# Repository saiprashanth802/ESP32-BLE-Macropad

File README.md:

# ESP32 BLE HID MacroPad

> An open-source, battery-powered wireless BLE HID macro pad built on ESP32 with NimBLE stack. Hand-wired with a custom FDM-printed enclosure, fully self-contained shortcut controller with an on-device UI — no companion app required.

---

## Versions

Every version lives side by side in this repo — `firmware/v4/`, `firmware/v5/`,
`cad/stl/v5/` and so on. **`main` is always the latest working state**; released
versions are marked with **git tags**, so you can grab any of them:

```bash
git clone https://github.com/saiprashanth802/ESP32-BLE-Macropad.git
git checkout v4.1     # or v5.0 — see Releases for downloadable zips
```

| Version | Tag | Status | Description |
|---------|-----|--------|-------------|
| v3 | — | ✅ Complete | 8-button, ST7735 128×160, ESP32-BLE-Keyboard — flagship build |
| v4 | `v4.1` | ✅ Stable | NimBLE stack, ghost connection fix, BUILD MODE |
| v4 + Media Remote | — | 🔬 Testing | Wireless AS5600 scroll wheel via ESP-NOW |
| v5 | `v5.0` | ✅ Built & Running | 12-key MX matrix, ST7789 240×320, multi-host BLE, robot face, Windows companion app |
| v5.1 | `v5.1` | ✅ Current | Local-LLM rewrite menu driven from the pad, wireless encoder puck complete |

---

## v3 — Flagship Build

> Primary portfolio entry. 8-button macro pad with ST7735 display, NimBLE BLE HID, and on-device preset switching with BUILD MODE.

### Build Photos

| | |
|---|---|
|  |  |
| Assembled v3 | Internal wiring |

| | |
|---|---|
|  |  |
| Enclosure CAD | Encoder knob CAD |

### Hardware
- ESP32 WROOM-32
- ST7735 128×160 TN display
- 8× tactile switches in 4×2 layout
- EC11 rotary encoder + custom skull knob
- TP4056 + 18650 2600mAh battery
- M3 corner studs with heat-set inserts
- Hand-wired, FDM printed enclosure (PLA, 0.2mm, 20% gyroid)

### Features
- 8 presets: OnShape, KiCad, Music, Gaming, LTspice, SYS, DEV, EDIT
- BUILD MODE — remap any button live (hold encoder 1.5s)
- Encoder modes: VOL / SCROLL / ZOOM / ALT-TAB
- Settings menu: brightness, sleep timeout, sensitivity, OS layout
- OS Layout: Windows / Linux — remaps shortcuts live
- RTOS light-sleep with GPIO wakeup
- Wake-key buffer + reconnect HUD
- BLE bond clear (hold encoder 3s)
- Estimated battery life: 3–4 months typical desk use

### GPIO Allocation (v3/v4)

| GPIO | Function |
|------|----------|
| 14,13,26,25,22,21,35,19 | 8× buttons |
| 2, 4 | Encoder CLK, DT |
| 15 | Encoder SW |
| 5, 17, 16, 12 | TFT CS, DC, RST, BL |
| 23, 18 | SPI MOSI, SCLK |

---

## v4 — Current Stable

> Migrated to NimBLE-Arduino to fix persistent BLE ghost-connection bug on Windows sleep/wake cycles.

### Key Changes from v3
- NimBLE-Arduino replaces ESP32-BLE-Keyboard
- GAP-layer callbacks for reliable connect/disconnect tracking
- 1N5819 Schottky diode on VIN rail isolating charger from USB supply
- `esp_sleep_disable_wakeup_source()` before re-arming GPIO wakeup each cycle
- `ledcAttach()` called on every wake to restore PWM backlight
- Firmware: `macropad_v4_nimble_espnow.ino`

### TFT_eSPI User_Setup.h

```cpp
#define ST7735_DRIVER
#define TFT_CS   5
#define TFT_DC   17
#define TFT_RST  16
#define TFT_WIDTH  128
#define TFT_HEIGHT 160
#define TFT_MOSI 23
#define TFT_SCLK 18
```

---

## Media Remote — Test Phase

> Standalone wireless scroll wheel using AS5600 magnetic encoder. Connects to v4 macropad via ESP-NOW or directly to PC via BLE HID. Designed for high-resolution smooth scrolling with velocity-based acceleration.

### Hardware
- ESP32 NodeMCU dev board
- AS5600 magnetic rotary encoder (I2C, 12-bit resolution, 4096 steps/rev)
- Custom 3D printed enclosure with bearing-mounted 50mm scroll wheel
- Diametrically magnetized cylinder magnet on axle
- 3× tactile buttons — Play/Pause, Next, Prev

### Design & Prototype

| | |
|---|---|
|  |  |
| Enclosure CAD | Scroll wheel with bearing mount CAD |

*Prototype — printed enclosure with 50mm scroll wheel, AS5600 underneath, wired to NodeMCU ESP32S*

### Features
- Velocity-accelerated volume control — slow turn = fine steps, fast spin = large jumps
- Adjustable sensitivity 1–10, saved to NVS
- Hold Btn1 + turn wheel = adjust sensitivity live
- Hold Btn1 + Btn3 for 1.5s = toggle ESP-NOW ↔ BLE mode
- Mode and sensitivity persist across power cycles
- LED blink feedback: 1 blink = ESP-NOW, 3 blinks = BLE

### Modes

| Mode | Description |
|------|-------------|
| BLE HID | Connects directly to PC as "MediaRemote" |
| ESP-NOW | Sends to v4 macropad which relays via BLE to PC |

### Wiring

| Pin | GPIO | Function |
|-----|------|----------|
| AS5600 SDA | 21 | I2C data |
| AS5600 SCL | 22 | I2C clock |
| BTN1 Play/Pause | 27 | INPUT_PULLUP → GND |
| BTN2 Next | 26 | INPUT_PULLUP → GND |
| BTN3 Prev | 25 | INPUT_PULLUP → GND |
| LED | 2 | Onboard LED |

---

## v5 — Built & Running

> Full redesign, **assembled and working**. 12-key MX mechanical switch matrix (4×3 landscape), ST7789 240×320 IPS display, **multi-host BLE with 3 device slots (Logitech Easy-Switch style)**, a state-reactive robot face with personalities, and a Windows companion app that turns the pad into a Stream Deck.

### Build Photos

| | |
|---|---|
|  |  |
| Assembled v5 — printed case, spiral-top keycaps, blue accent lighting | Top-down: 4×3 MX grid and the 2" IPS display |

*The screen shows the pad's two live features at once: the procedural robot eyes in
their default robotic blue, and the now-playing strip — track title with a progress
bar and elapsed/total time, streamed from the host by the companion app.*

**Print files:** [`cad/stl/v5/`](cad/stl/v5) — three case parts plus the switch plate.

### Multi-Host BLE — use it like a Pebble Keys
- 3 host slots, each remembers one bonded device (NVS persisted across power cycles)
- Hold **FN (K9) 1s** → tap **K1/K2/K3** to jump between paired devices
- Hold the slot key 1.5s instead to (re-)pair that slot with a new device
- **Each slot advertises its own static-random BLE address**, so every host stores an independent bond. This is what makes the slots real: with one shared identity, two OSes dual-booting the same machine present the *same* controller MAC, collapse onto one slot, and each re-pair overwrites the other's link key — the endless forget-and-re-pair loop
- Switching re-advertises **open** (no accept-list — whitelist filtering breaks reconnection from resolvable private addresses); a bonded host that belongs to a different slot is rejected in software
- Status bar shows the three slots like Easy-Switch LEDs (green = connected, amber = waiting, magenta = pairing)
- Firmware: `firmware/v5/macropad_v5.ino` (NimBLE 2.x API, single file)

### Face — state-reactive robot eyes / GIF screensaver
- Procedural eyes that react to device state: blink when idle-connected, dart when disconnected, widen in pairing mode, glance toward the slot on Easy-Switch, droop before sleep
- **Expression packs**: every eye parameter (color, geometry, blink/glance timing) is JSON in the config API — the companion app can generate personalities without reflashing
- Or upload a looping **GIF** (≤ ~700 KB) through the web UI as an ambient screensaver
- Settings → FACE (OFF/IDLE/ALWAYS) and STYLE (EYES/GIF); first press always just wakes, never types
- Custom partition table: dual 1.5 MB OTA slots + 896 KB SPIFFS for animations

### Rewrite Menu — local LLM text tools, driven from the pad
- Select text anywhere, press a key on the pad, pick a style — the pad rewrites it in place
- Styles: formalise, casualise, shorten, clarify, fix spelling/grammar, summarise, expand rough notes into an email, or treat the selection as a prompt and answer it
- Runs against a local **[Ollama](https://ollama.com)** instance, so **nothing leaves the machine** unless a style is deliberately pointed at a hosted model
- Prompts, temperature, reasoning and per-style model live in a **hot-reloaded `styles.json`** — tune them without a rebuild
- Pad shows the style picker, then ACCEPT / REGEN / CANCEL; the side-by-side preview on screen is editable before you accept
- Built entirely on the existing host-link opcodes — **no firmware changes required**
- A **fine-tuned FIX model** was trained for this and measured against the general-purpose
  one across two sizes and four epoch counts. It wins on corrections and speed and loses on
  restraint, which is the axis that decides — so it did not ship, and the lab is in the repo
  anyway: [`ml/`](ml) and [`docs/FIX_MODEL_FINETUNE.md`](docs/FIX_MODEL_FINETUNE.md)
- Full guide: [`docs/REWRITE_MENU.md`](docs/REWRITE_MENU.md) · Linux setup:
  [`docs/LINUX_REWRITE_SETUP.md`](docs/LINUX_REWRITE_SETUP.md)

### Companion App — Windows and Linux

> The pad works standalone. The companion turns it into a Stream Deck: it launches
> and focuses apps from a key press, streams now-playing to the pad's screen,
> switches presets to follow the foreground window, feeds the puck a real volume
> number, and drives the rewrite menu.

- Two front-ends over one shared **.NET 9** core — `MacroPadDeck.Core` holds the wire
  protocol, profiles and orchestration; `MacroPadDeck` is WinRT/SMTC/WPF, and
  `MacroPadDeck.Linux` is BlueZ/MPRIS/X11/GTK3
- **Install, build and run:** [`companion/README.md`](companion/README.md) — .NET 9 SDK
  per platform, the dependencies, pairing, the publish command, and what each failure
  in `deck.log` means

### Config Mode — wireless setup + OTA firmware update
- **Settings → CONFIG (WiFi/OTA)** suspends BLE and raises a WiFi hotspot (`MacroPad-Setup` / `macropad123`, `http://192.168.4.1`)
- Built-in web UI + JSON API to remap keys, edit presets, and change settings — no re-flash needed
- Every key can be a built-in action, an **arbitrary modifier+keycode chord**, a media code, a **type-a-string**, or a **multi-step macro** — the schema a companion app targets
- **OTA firmware update**: upload a new `.bin` from the browser; it flashes the inactive OTA partition and reboots (safe rollback if it fails)
- WiFi and BLE never run at once (WROOM-32 coexistence); entering/leaving Config Mode reboots cleanly
- Full contract: [`docs/CONFIG_API.md`](docs/CONFIG_API.md)

### Wireless Encoder Puck — a dial that isn't attached to anything

| | |
|---|---|
|  |  |
| The puck beside the v5 — a separate battery-powered device, no cable between them | 50 mm dial in the two-part printed housing |

- **Separate device**, talks to the pad over **ESP-NOW** — no cable, no second BLE connection to manage
- **AS5600 magnetic angle sensor** — 12-bit, contactless, nothing mechanical to wear out. The magnet is diametrically magnetised and sits in a pocket in the dial
- **The pad owns the dial mode** (VOLUME / ZOOM). The puck renders whatever it's told and never self-changes, so a pad key and the puck can't disagree
- **Volume is pushed, never estimated.** BLE HID volume is relative — the pad sends up/down and is never told the level — so the companion reading Windows Core Audio is the only way either device knows a real number
- **Deep sleep when unlinked**, waking on rotation. The AS5600 has no motion interrupt, so waking is timer-poll-and-look with a movement threshold, which stops a knock or thermal drift waking it
- **Sealed housing with no reset button** — spinning the dial a few turns while unlinked reboots it. Gated strictly on being unlinked, since spinning hard is completely ordinary during normal volume use
- Wiring: [`hardware/puck_wiring.md`](hardware/puck_wiring.md) · Protocol: [`docs/PUCK_PROTOCOL.md`](docs/PUCK_PROTOCOL.md) · Print files: [`cad/stl/puck/`](cad/stl/puck)

### Hardware Spec
- NodeMCU ESP32-S V1.1 (WROOM-32) dev board
- ST7789 240×320 IPS display, landscape mount, glass flush-mounted (30.6×40.8mm active area)
- 12× MX compatible mechanical switches, plate mount, 4×3 landscape matrix, 19.05mm pitch
- 12× 1N4148 diodes for n-key rollover (cathode → row line — see `hardware/pin_reference_v5.md`)
- Wireless encoder puck: AS5600 + 50mm bearing-mounted dial, ESP-NOW (separate device — **built and working**; see [`hardware/puck_wiring.md`](hardware/puck_wiring.md) and [`docs/PUCK_PROTOCOL.md`](docs/PUCK_PROTOCOL.md))
- CKCS charge+boost module + 18650 cell
- Custom copper-tape ridge substrate PCB

### Enclosure
- 115×95×30mm main body
- Encoder dial lobe: half-proud right edge, 50mm diameter, 25mm proud (XP-Pen style)
- Screen: 31.0×41.2mm flush glass window, 35.2×48.4mm module ledge 2.1mm deep
- Bottom cover: M3 screws into brass heat-set inserts, 4× corners

### PCB Technique — Copper Tape Ridge Substrate
3D printed plate with elevated ridges as trace isolation guides. A single copper sheet is laid over the entire surface — the ridges act as cutting guides. Scalpel-cut along ridge edges isolates traces. Looks like a real PCB, built from scratch.

### v5 GPIO Allocation

| GPIO | Board Label | Function | Notes |
|------|------------|----------|-------|
| 18 | P18 | TFT SCK | SPI clock |
| 23 | P23 | TFT MOSI | ST7789 SDA |
| 5  | P5  | TFT CS  | |
| 21 | P21 | TFT DC  | |
| 22 | P22 | TFT RST | |
| 19 | P19 | TFT BL  | PWM via LEDC |
| 25 | P25 | Matrix Row 1 | Driven LOW to scan |
| 26 | P26 | Matrix Row 2 | Driven LOW to scan |
| 27 | P27 | Matrix Row 3 | Driven LOW to scan |
| 32 | P32 | Matrix Row 4 | Driven LOW to scan |
| 33 | P33 | Matrix Col 1 | INPUT_PULLUP |
| 13 | P13 | Matrix Col 2 | INPUT_PULLUP |
| 14 | P14 | Matrix Col 3 | INPUT_PULLUP |

> Zero strapping pins used — clean boot every time, no pull resistors needed for boot. No I2C or encoder switch on the main board — the AS5600 puck is wireless. Full details + diode orientation: `hardware/pin_reference_v5.md`.

---

## Repository Structure

```
ESP32-BLE-MacroPad/
├── firmware/
│   ├── v4/macropad_v4_nimble_espnow.ino   — v4 + optional ESP-NOW
│   ├── v5/
│   │   ├── macropad_v5/                   — v5 multi-host firmware + partition table
│   │   ├── puck_encoder/                  — wireless encoder puck (ESP32)
│   │   ├── puck_encoder_8266/             — puck on ESP-12E
│   │   └── User_Setup.h                   — TFT_eSPI config for the ST7789
│   ├── media_remote/                      — BLE + ESP-NOW scroll wheel
│   └── tests/                             — per-peripheral bring-up sketches
├── companion/
│   ├── README.md                          — install / build / run — start here
│   ├── MacroPadDeck.Core/                 — protocol, profiles, controller (net9.0)
│   ├── MacroPadDeck/                      — Windows front-end (WinRT/WPF)
│   └── MacroPadDeck.Linux/                — Linux front-end (BlueZ/MPRIS/GTK3)
├── ml/                                    — the FIX fine-tune lab: data generator,
│                                            eval harness, training configs, runbook
├── cad/stl/                               — print files: v5 case, keycaps, puck
├── hardware/
│   ├── pin_reference_v5.md                — complete v5 GPIO table + diode orientation
│   ├── puck_wiring.md                     — encoder puck wiring
│   ├── kicad/                             — KiCad project + fab gerbers
│   ├── datasheets/                        — ESP-12E
│   └── ESP32_DevKitC_v4.kicad_mod         — custom KiCad footprint
├── docs/
│   ├── CONFIG_API.md                      — host-link opcodes and the JSON config API
│   ├── REWRITE_MENU.md                    — local-LLM text tools
│   ├── LINUX_REWRITE_SETUP.md             — ydotool / Wayland one-time setup
│   ├── FIX_MODEL_FINETUNE.md              — the fine-tune, measured, and why it lost
│   ├── PUCK_PROTOCOL.md                   — ESP-NOW protocol v3
│   └── ROADMAP.md · TESTING_LOG.md
├── scripts/setup-ydotool.sh
└── README.md
```

---

## Dependencies

| Library | Purpose |
|---------|---------|
| NimBLE-Arduino | BLE HID stack |
| TFT_eSPI | Display driver |
| Preferences | NVS persistent storage |
| Wire | I2C for AS5600 |
| esp_now | ESP-NOW for media remote |

Companion app (see [`companion/README.md`](companion/README.md)):

| Requirement | Purpose |
|---------|---------|
| .NET 9 SDK | Builds all three companion projects |
| BlueZ / WinRT | BLE host link to the pad |
| GTK3 + libayatana-appindicator | Linux tray and editor |
| MPRIS / SMTC | Now-playing source |
| Ollama (optional) | Local model behind the rewrite menu |

---

## Key Learnings

- **NimBLE vs ESP32-BLE-Keyboard** — NimBLE with GAP callbacks is required for reliable connect/disconnect tracking. The Arduino BLE stack returns false positives after Windows sleep/wake.
- **GPIO 12 strapping pin** — Must read LOW at boot. Avoided entirely in v5 by moving TFT backlight to GPIO 19.
- **LEDC + BLE init order** — BLE radio init resets the LEDC peripheral. Always call `ledcAttach()` after `NimBLEDevice::init()`.
- **WiFi + BLE coexistence** — ESP-NOW and NimBLE share the antenna. Made optional in v4 (toggle in settings) to avoid connection instability.
- **ST7789 RAM constraint** — Full 240×320 16-bit sprite = 153KB, too large for WROOM-32 with BLE active. Solution: direct TFT drawing with small reusable sprites.
- **Input-only GPIOs** — GPIO 34, 35, 36, 39 have no internal pullups. Always use external 10kΩ resistors.

---

## License

**CC BY-NC 4.0** — Free to use and modify for personal and non-commercial purposes only. Commercial use requires explicit written permission from the author.

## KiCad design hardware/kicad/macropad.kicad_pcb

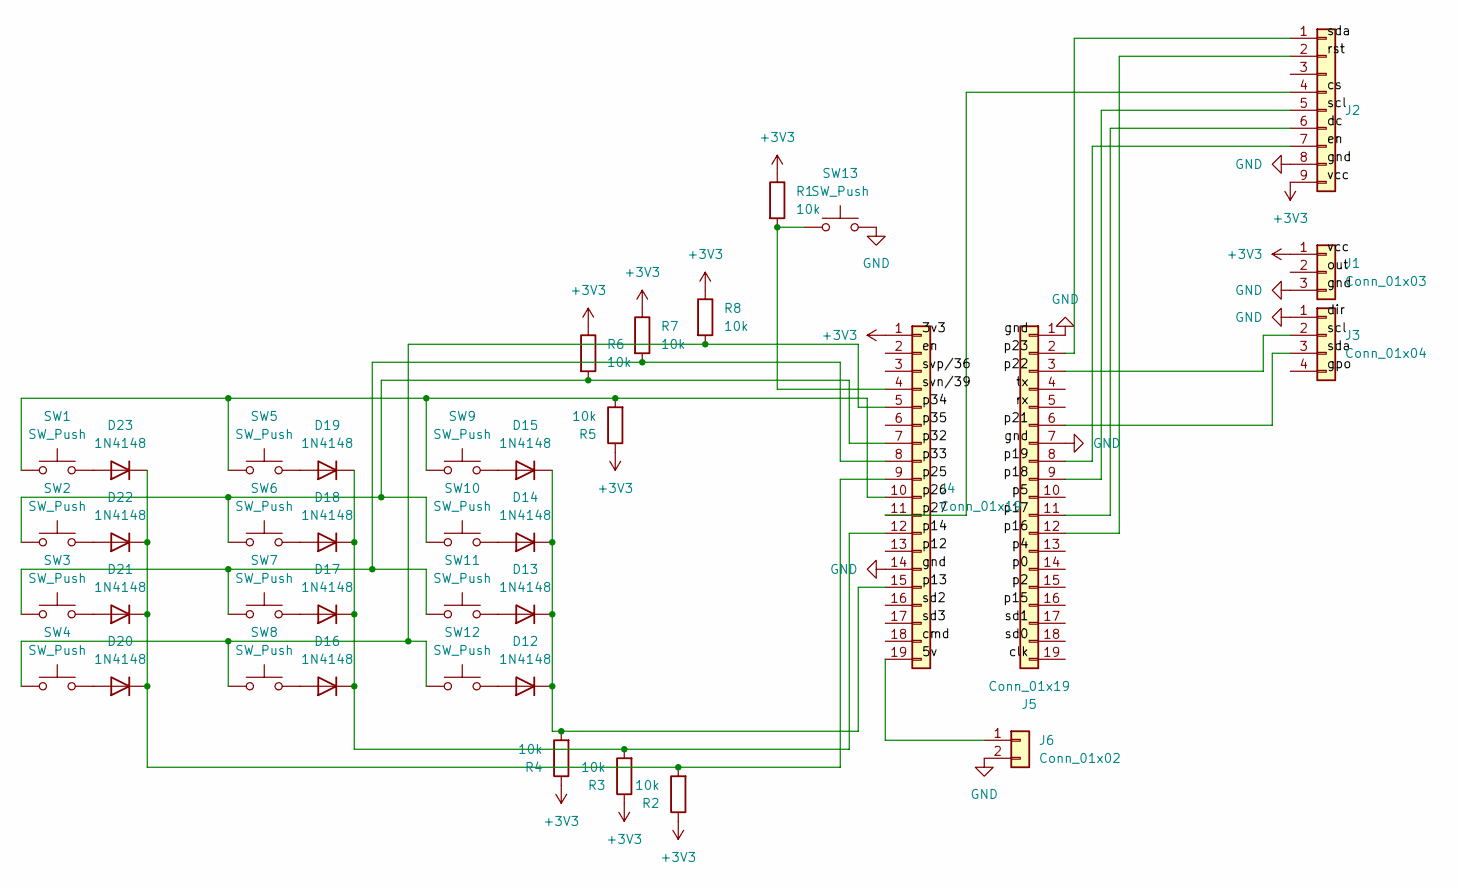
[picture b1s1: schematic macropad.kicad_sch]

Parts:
D12, D13, D14, D15, D16, D17, D18, D19, D20, D21, D22, D23: 1N4148; D_DO-35_SOD27_P7.62mm_Horizontal
J1: Conn_01x03; PinHeader_1x03_P2.54mm_Vertical
J2: Conn_01x09; PinHeader_1x09_P2.54mm_Vertical
J3: Conn_01x04; PinHeader_1x04_P2.54mm_Vertical
J4, J5: Conn_01x19; PinHeader_1x19_P2.54mm_Horizontal
J6: Conn_01x02; PinHeader_1x02_P2.54mm_Horizontal
R1, R2, R3, R4, R5, R6, R7, R8: 10k; R_Axial_DIN0207_L6.3mm_D2.5mm_P7.62mm_Horizontal
SW1, SW2, SW3, SW4, SW5, SW6, SW7, SW8, SW9, SW10, SW11, SW12: SW_Push; SW_Cherry_MX_1.00u_PCB
SW13: SW_Push; SW_PUSH_6mm_H4.3mm

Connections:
+3V3: J1.1, J2.9, J4.1, R1.1, R2.1, R3.1, R4.1, R5.1, R6.1, R7.1, R8.1
/p27: J2.4, J4.11
GND: J1.3, J2.8, J3.1, J4.14, J5.1, J5.7, J6.2, SW13.2
unnamed: D12.2 (A), SW12.2
unnamed: D12.1 (K), D13.1 (K), D14.1 (K), D15.1 (K), J4.15, R4.2
unnamed: D13.2 (A), SW11.2
unnamed: D14.2 (A), SW10.2
unnamed: D15.2 (A), SW9.2
unnamed: D16.2 (A), SW8.2
unnamed: D16.1 (K), D17.1 (K), D18.1 (K), D19.1 (K), J4.12, R3.2
unnamed: D17.2 (A), SW7.2
unnamed: D18.2 (A), SW6.2
unnamed: D19.2 (A), SW5.2
unnamed: D20.2 (A), SW4.2
unnamed: D20.1 (K), D21.1 (K), D22.1 (K), D23.1 (K), J4.9, R2.2
unnamed: D21.2 (A), SW3.2
unnamed: D22.2 (A), SW2.2
unnamed: D23.2 (A), SW1.2
unnamed: J2.1, J5.2
unnamed: J2.2, J5.12
unnamed: J2.5, J5.9
unnamed: J2.6, J5.11
unnamed: J2.7, J5.8
unnamed: J3.2, J5.3
unnamed: J3.3, J5.6
unnamed: J4.4, R1.2, SW13.1
unnamed: J4.5, R8.2, SW4.1, SW8.1, SW12.1
unnamed: J4.7, R6.2, SW2.1, SW6.1, SW10.1
unnamed: J4.8, R7.2, SW3.1, SW7.1, SW11.1
unnamed: J4.10, R5.2, SW1.1, SW5.1, SW9.1
unnamed: J4.19, J6.1

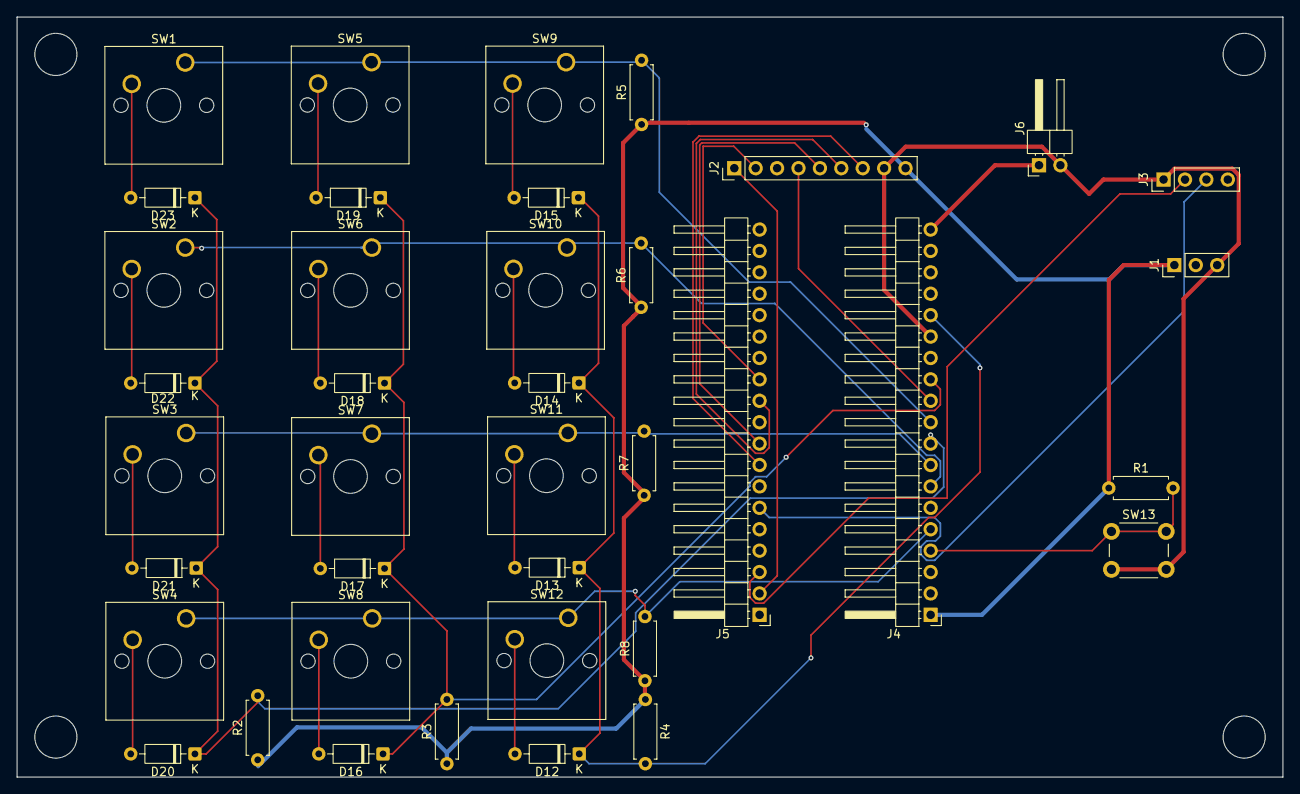
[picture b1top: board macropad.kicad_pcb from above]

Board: 2 copper layers, 150.2 x 90.2 mm, 39 parts (0 on the bottom side), 31 nets.

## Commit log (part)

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2026-04-09 v2 hardware + v3 firmware + all STL print files
2026-04-09 Rename cad_body .png to cad_body.png
2026-05-02 v4.1: fix ghost BLE connection + sleep cycle bug
2026-06-02 Add v5 hardware, media remote, test sketches, docs
2026-06-02 Update README with all images, media remote section, v5 spec
